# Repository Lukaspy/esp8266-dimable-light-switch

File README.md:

# esp8266-dimable-light-switch
A dimmable wifi connected light switch

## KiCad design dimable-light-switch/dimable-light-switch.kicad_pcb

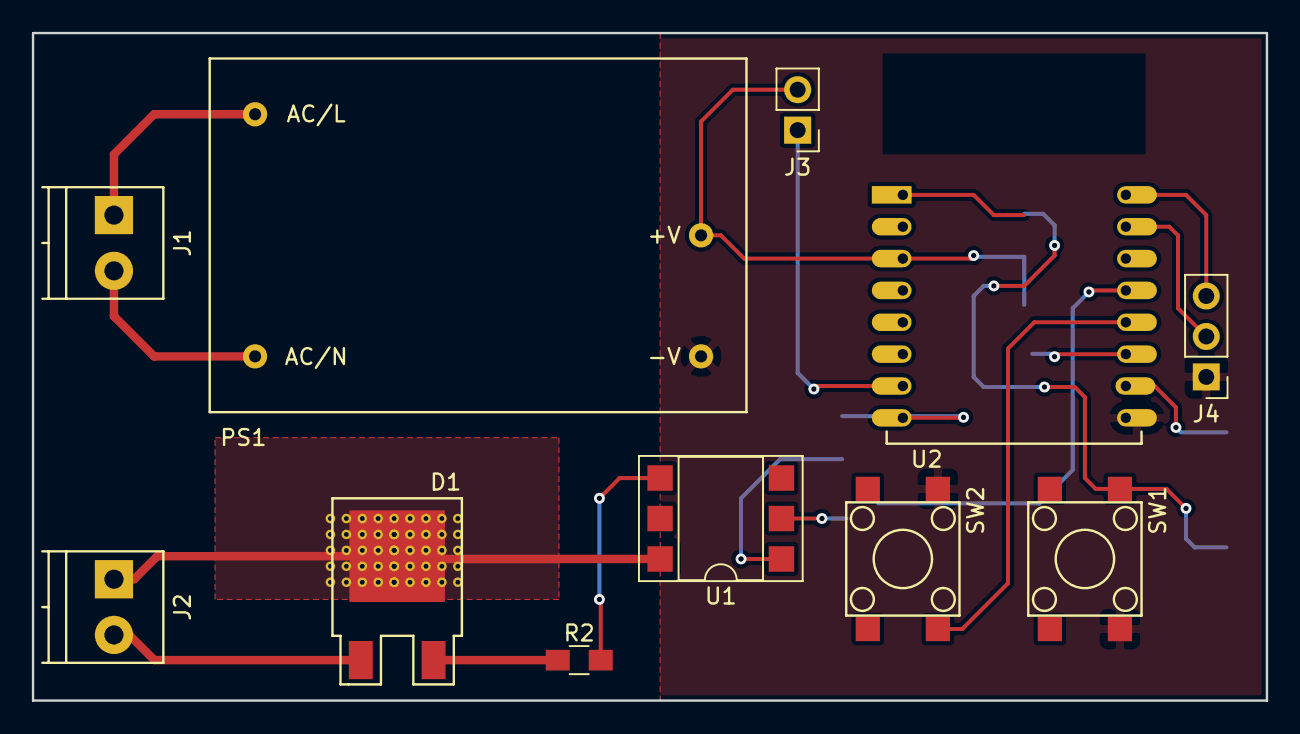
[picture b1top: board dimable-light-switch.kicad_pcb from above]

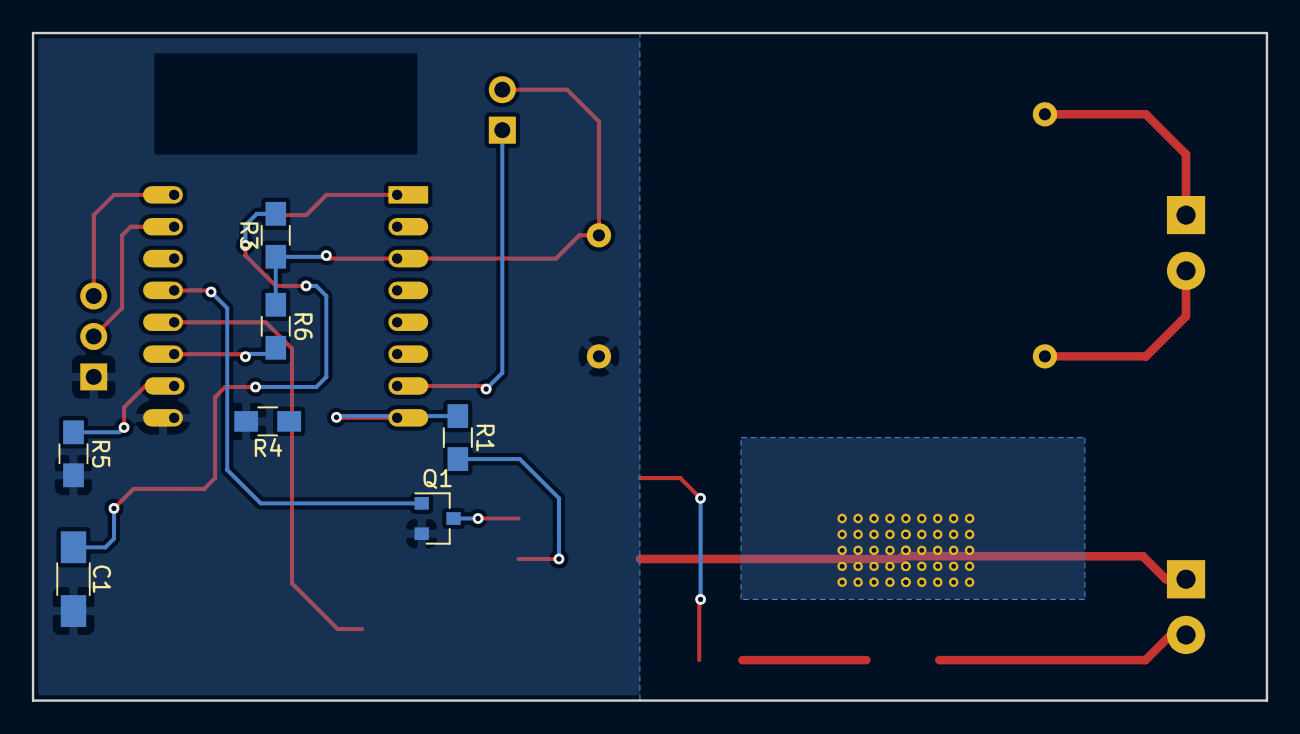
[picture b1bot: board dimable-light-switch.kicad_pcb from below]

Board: 2 copper layers, 77.5 x 41.9 mm, 18 parts (7 on the bottom side), 18 nets.

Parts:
C1: 0.1uF; C_1206_HandSoldering
D1: BTA204S; SOT428
J1, J2: Screw_Terminal; TerminalBlock_Phoenix_PT-3.5mm_2pol
J3: Conn_Switch; Pin_Header_Straight_1x02_Pitch2.54mm
J4: Conn_Prog; Pin_Header_Straight_1x03_Pitch2.54mm
PS1: IRM-01-3.3
Q1: MMBT3904; SOT-23
R1: 560R; R_0805_HandSoldering
R2: 220R; R_0805_HandSoldering
R3, R4, R6: 10K; R_0805_HandSoldering
R5: 1K; R_0805_HandSoldering
SW1, SW2: SW_Push; TactileButtonSMD
U1: MOC3051M; DIP-6_W7.62mm_SMDSocket_SmallPads
U2: ESP-12S; ESP-12

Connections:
+3V3: J3.2, PS1.3, R1.1, R3.1, R6.1, U2.3, U2.8
GND: C1.2, J4.1, PS1.4, Q1.2, R4.2, R5.2, SW1.1, SW2.2, U2.9
GPIO4: Q1.1, U2.13
unnamed: C1.1, R3.2, SW1.2, U2.1
unnamed: D1.1, J2.2
unnamed: D1.2, J2.1, U1.6
unnamed: D1.3, R2.1
unnamed: J1.1, PS1.1
unnamed: J1.2, PS1.2
unnamed: J3.1, U2.7
unnamed: J4.2, U2.15
unnamed: J4.3, U2.16
unnamed: Q1.3, U1.2
unnamed: R1.2, U1.1
unnamed: R2.2, U1.4
unnamed: R5.1, U2.10
unnamed: R6.2, U2.11
unnamed: SW2.1, U2.12

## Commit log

2018-03-03 Create Kicad Project Files and Draw Schematic.
2018-03-03 Assign/Create Footprints
2018-03-03 PCB Routing
